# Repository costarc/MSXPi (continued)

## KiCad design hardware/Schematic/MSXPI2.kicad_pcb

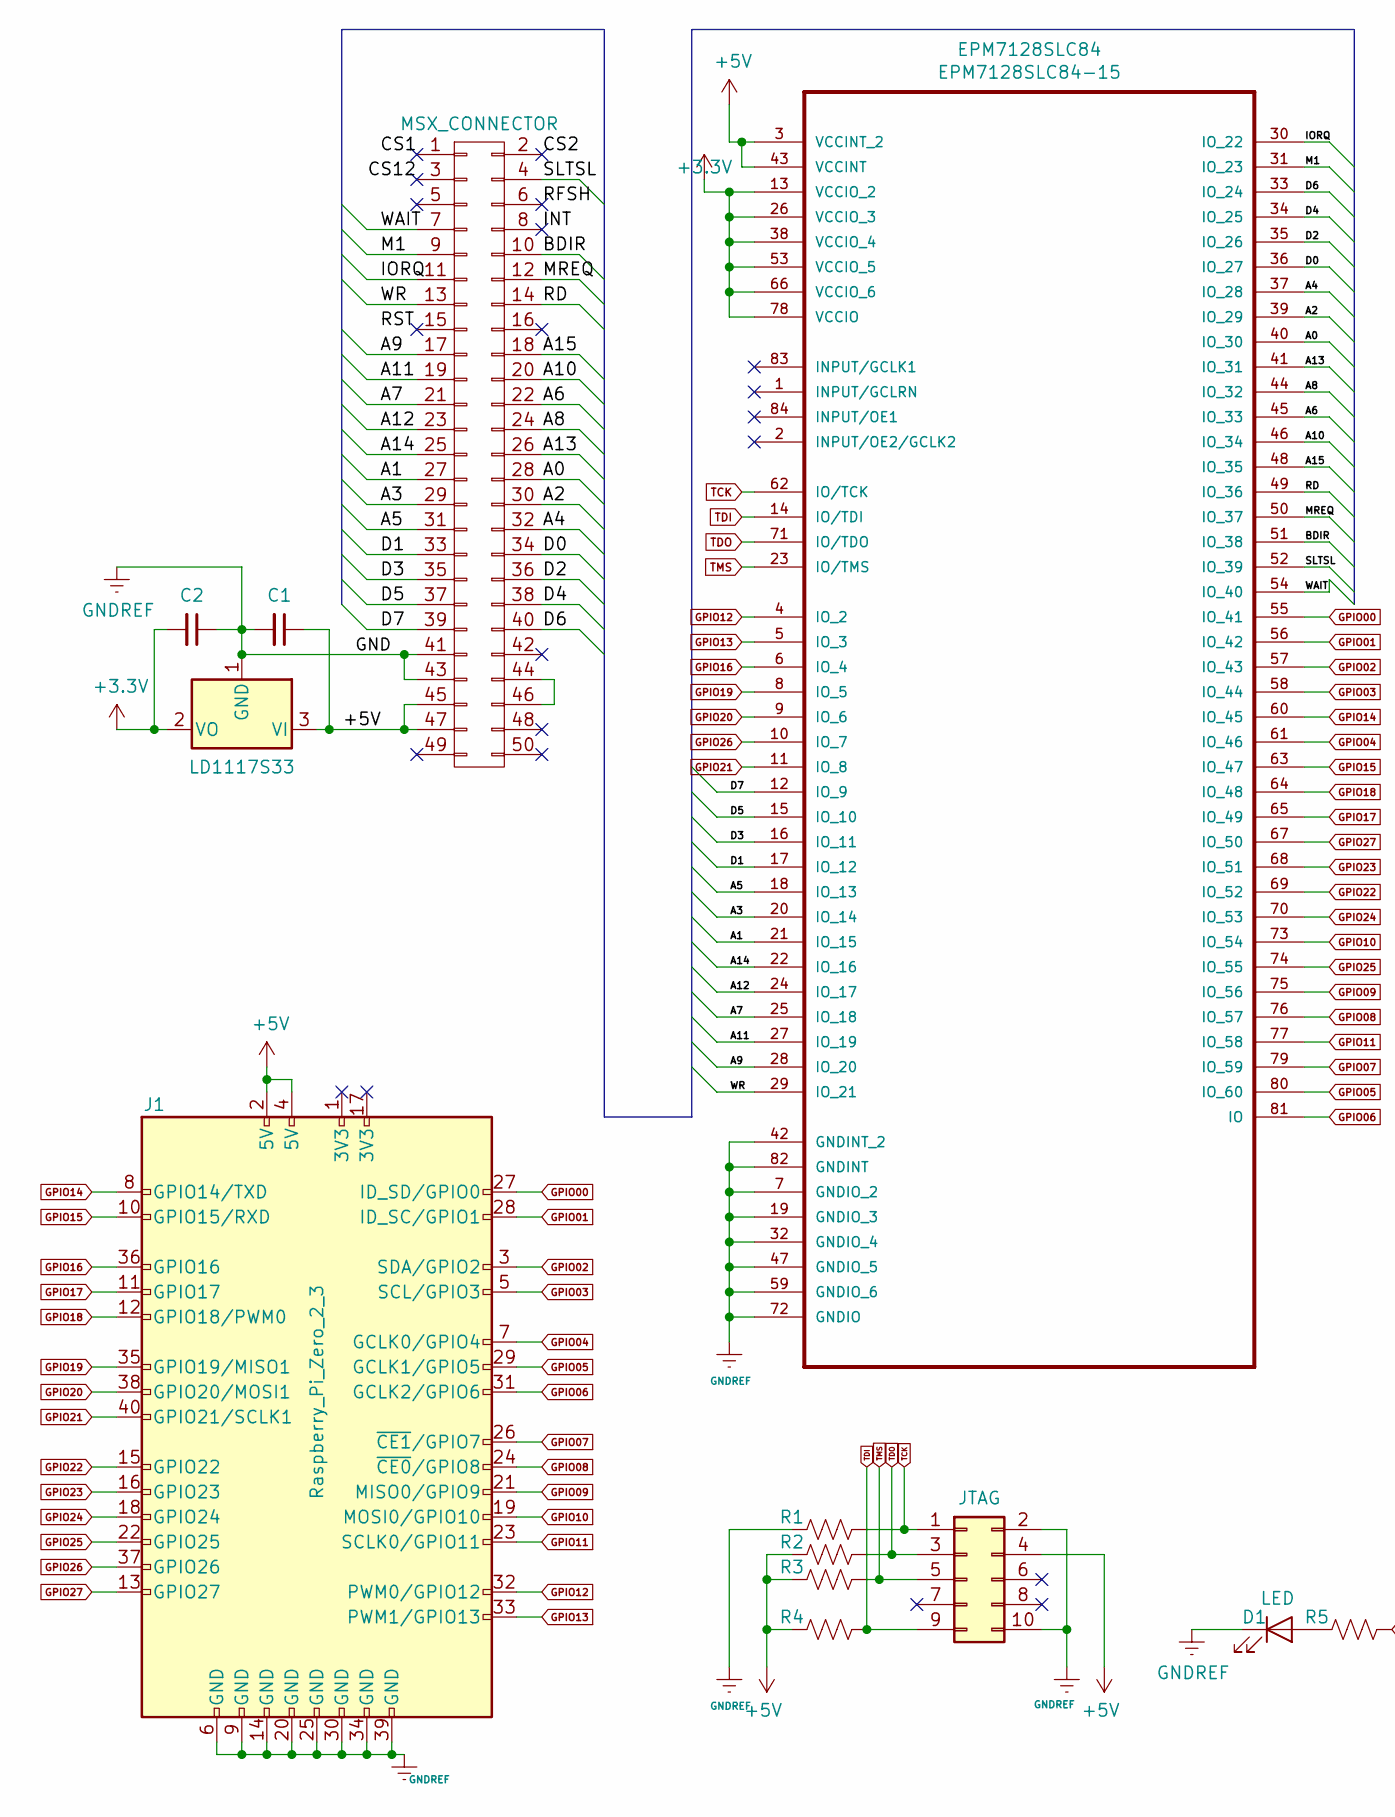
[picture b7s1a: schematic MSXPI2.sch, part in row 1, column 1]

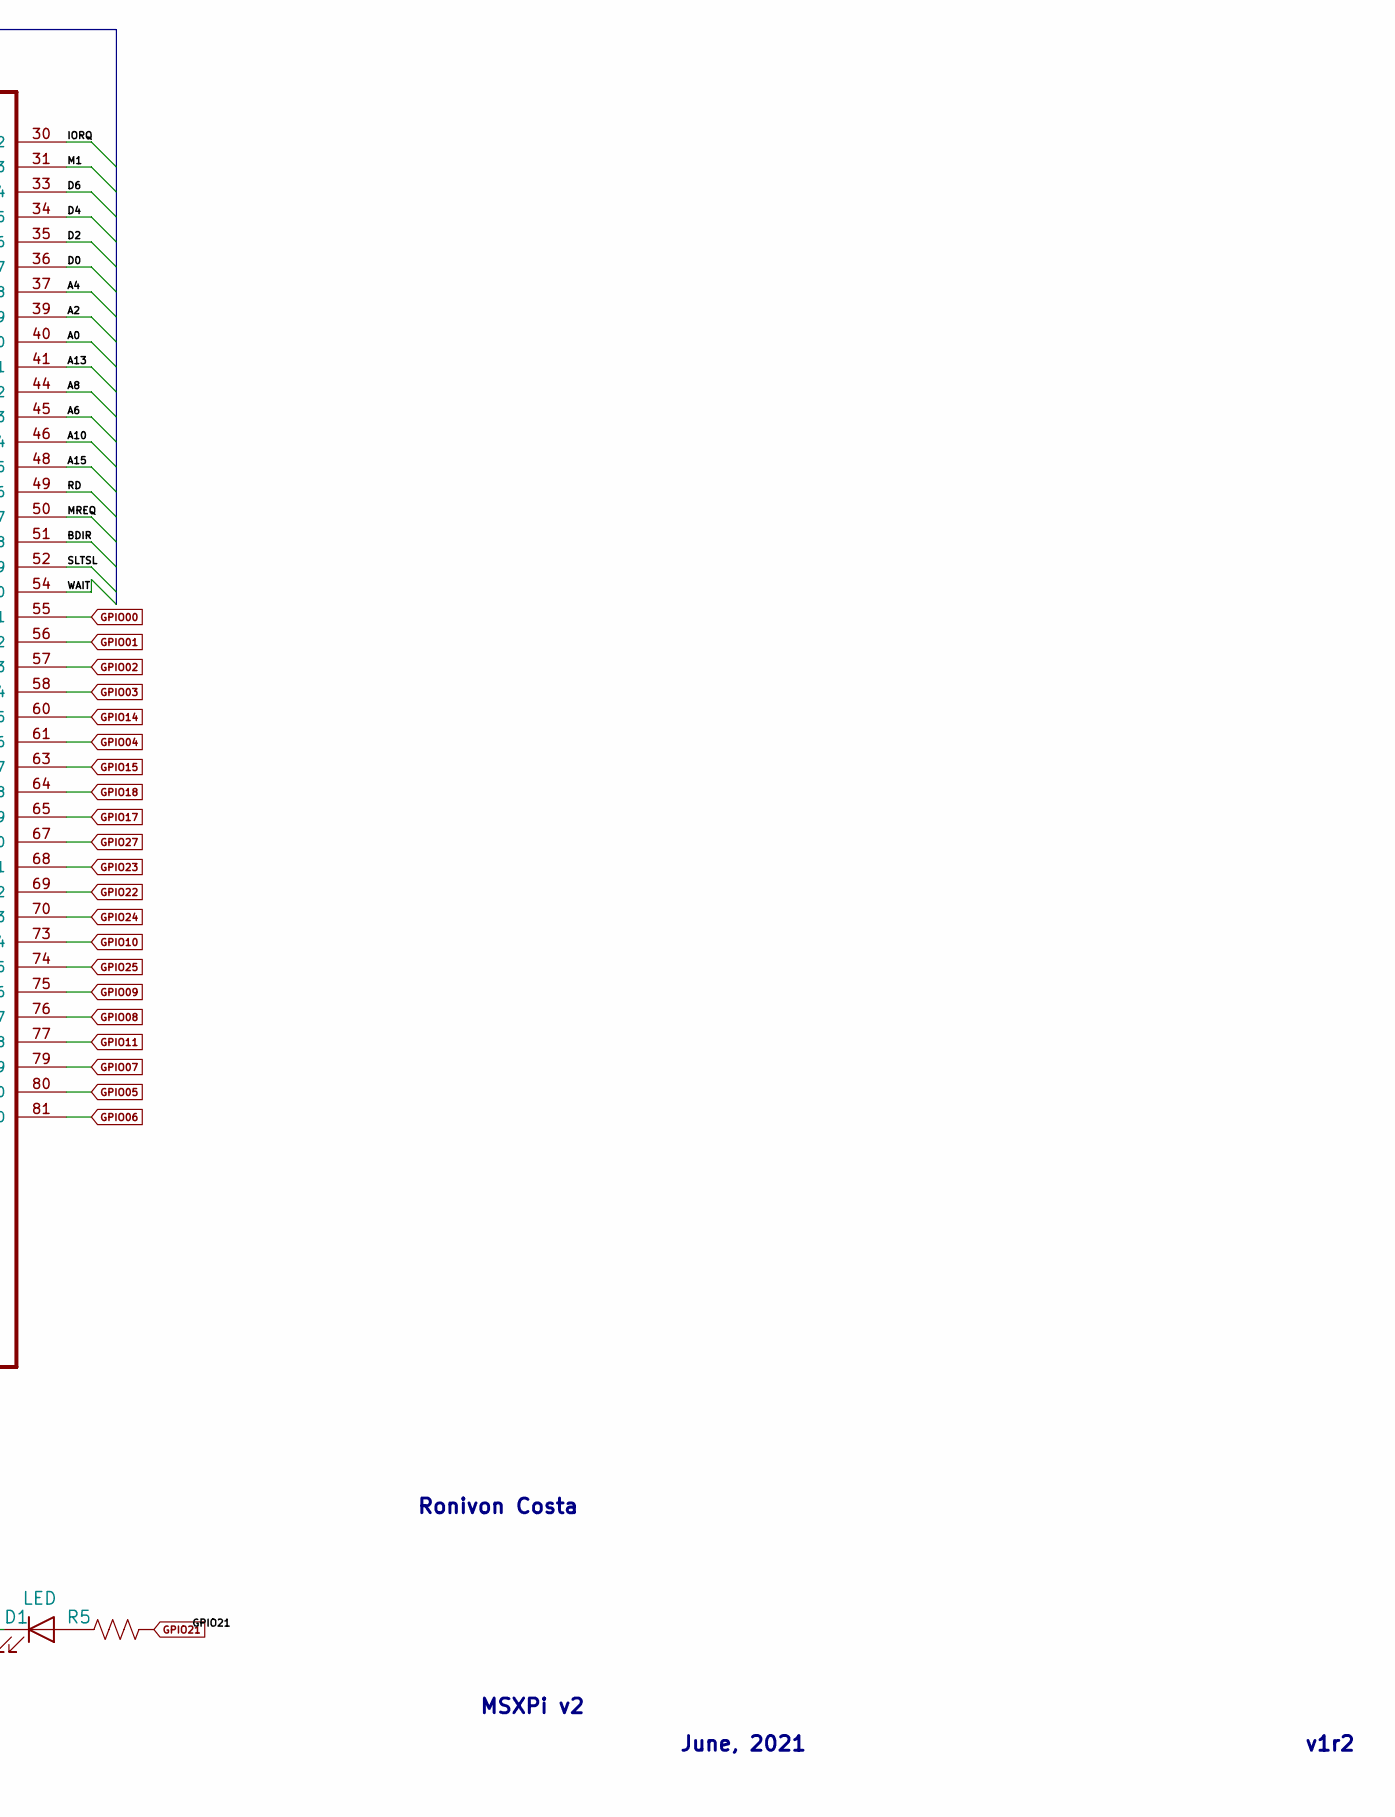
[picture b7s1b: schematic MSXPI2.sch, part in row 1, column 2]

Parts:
C1: C1; C_Disc_D3.0mm_W1.6mm_P2.50mm
C2: C2; C_Disc_D3.0mm_W1.6mm_P2.50mm
D1: LED; LED_D3.0mm
EPM7128SLC84: EPM7128SLC84-15; PLCC-84_THT-Socket
J1: Raspberry_Pi_Zero_2_3; PinHeader_2x20_P2.54mm_Vertical
J2: JTAG; PinHeader_2x05_P2.54mm_Vertical
LD1117S33: LD1117S33TR_SOT223; SOT-223-3_TabPin2
P1: MSX_CONNECTOR; card_edge_connector
R1, R2, R3, R4, R5: R_US; R_Axial_DIN0204_L3.6mm_D1.6mm_P5.08mm_Horizontal

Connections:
+3V3: C2.2, EPM7128SLC84.13 (VCCIO_2), EPM7128SLC84.26 (VCCIO_3), EPM7128SLC84.38 (VCCIO_4), EPM7128SLC84.53 (VCCIO_5), EPM7128SLC84.66 (VCCIO_6), EPM7128SLC84.78 (VCCIO), LD1117S33.2 (VO)
+5V: C1.1, EPM7128SLC84.3 (VCCINT_2), EPM7128SLC84.43 (VCCINT), J1.2 (5V), J1.4 (5V), J2.4, LD1117S33.3 (VI), P1.45, P1.47, R2.2, R3.2, R4.2
/A0: EPM7128SLC84.40 (IO_30), P1.28
/A1: EPM7128SLC84.21 (IO_15), P1.27
/A2: EPM7128SLC84.39 (IO_29), P1.30
/A3: EPM7128SLC84.20 (IO_14), P1.29
/A4: EPM7128SLC84.37 (IO_28), P1.32
/A5: EPM7128SLC84.18 (IO_13), P1.31
/A6: EPM7128SLC84.45 (IO_33), P1.22
/A7: EPM7128SLC84.25 (IO_18), P1.21
/A8: EPM7128SLC84.44 (IO_32), P1.24
/A9: EPM7128SLC84.28 (IO_20), P1.17
/A10: EPM7128SLC84.46 (IO_34), P1.20
/A11: EPM7128SLC84.27 (IO_19), P1.19
/A12: EPM7128SLC84.24 (IO_17), P1.23
/A13: EPM7128SLC84.41 (IO_31), P1.26
/A14: EPM7128SLC84.22 (IO_16), P1.25
/A15: EPM7128SLC84.48 (IO_35), P1.18
/BDIR: EPM7128SLC84.51 (IO_38), P1.10
/D0: EPM7128SLC84.36 (IO_27), P1.34
/D1: EPM7128SLC84.17 (IO_12), P1.33
/D2: EPM7128SLC84.35 (IO_26), P1.36
/D3: EPM7128SLC84.16 (IO_11), P1.35
/D4: EPM7128SLC84.34 (IO_25), P1.38
/D5: EPM7128SLC84.15 (IO_10), P1.37
/D6: EPM7128SLC84.33 (IO_24), P1.40
/D7: EPM7128SLC84.12 (IO_9), P1.39
/IORQ: EPM7128SLC84.30 (IO_22), P1.11
/M1: EPM7128SLC84.31 (IO_23), P1.9
/MREQ: EPM7128SLC84.50 (IO_37), P1.12
/RD: EPM7128SLC84.49 (IO_36), P1.14
/SLTSL: EPM7128SLC84.52 (IO_39), P1.4
/WAIT: EPM7128SLC84.54 (IO_40), P1.7
/WR: EPM7128SLC84.29 (IO_21), P1.13
GNDREF: C1.2, C2.1, D1.1 (K), EPM7128SLC84.7 (GNDIO_2), EPM7128SLC84.19 (GNDIO_3), EPM7128SLC84.32 (GNDIO_4), EPM7128SLC84.42 (GNDINT_2), EPM7128SLC84.47 (GNDIO_5), EPM7128SLC84.59 (GNDIO_6), EPM7128SLC84.72 (GNDIO), EPM7128SLC84.82 (GNDINT), J1.6 (GND), J1.9 (GND), J1.14 (GND), J1.20 (GND), J1.25 (GND), J1.30 (GND), J1.34 (GND), J1.39 (GND), J2.2, J2.10, LD1117S33.1 (GND), P1.41, P1.43, R1.1
GPIO0: EPM7128SLC84.55 (IO_41), J1.27 (ID_SD/GPIO0)
GPIO1: EPM7128SLC84.56 (IO_42), J1.28 (ID_SC/GPIO1)
GPIO02: EPM7128SLC84.57 (IO_43), J1.3 (SDA/GPIO2)
GPIO03: EPM7128SLC84.58 (IO_44), J1.5 (SCL/GPIO3)
GPIO04: EPM7128SLC84.61 (IO_46), J1.7 (GCLK0/GPIO4)
GPIO05: EPM7128SLC84.80 (IO_60), J1.29 (GCLK1/GPIO5)
GPIO06: EPM7128SLC84.81 (IO), J1.31 (GCLK2/GPIO6)
GPIO07: EPM7128SLC84.79 (IO_59), J1.26 (~CE1~/GPIO7)
GPIO08: EPM7128SLC84.76 (IO_57), J1.24 (~CE0~/GPIO8)
GPIO09: EPM7128SLC84.75 (IO_56), J1.21 (MISO0/GPIO9)
GPIO10: EPM7128SLC84.73 (IO_54), J1.19 (MOSI0/GPIO10)
GPIO11: EPM7128SLC84.77 (IO_58), J1.23 (SCLK0/GPIO11)
GPIO12: EPM7128SLC84.4 (IO_2), J1.32 (PWM0/GPIO12)
GPIO13: EPM7128SLC84.5 (IO_3), J1.33 (PWM1/GPIO13)
GPIO14: EPM7128SLC84.60 (IO_45), J1.8 (GPIO14/TXD)
GPIO15: EPM7128SLC84.63 (IO_47), J1.10 (GPIO15/RXD)
GPIO16: EPM7128SLC84.6 (IO_4), J1.36 (GPIO16)
GPIO17: EPM7128SLC84.65 (IO_49), J1.11 (GPIO17)
GPIO18: EPM7128SLC84.64 (IO_48), J1.12 (GPIO18/PWM0)
GPIO19: EPM7128SLC84.8 (IO_5), J1.35 (GPIO19/MISO1)
GPIO20: EPM7128SLC84.9 (IO_6), J1.38 (GPIO20/MOSI1)
GPIO21: EPM7128SLC84.11 (IO_8), J1.40 (GPIO21/SCLK1), R5.2
GPIO22: EPM7128SLC84.69 (IO_52), J1.15 (GPIO22)
GPIO23: EPM7128SLC84.68 (IO_51), J1.16 (GPIO23)
GPIO24: EPM7128SLC84.70 (IO_53), J1.18 (GPIO24)
GPIO25: EPM7128SLC84.74 (IO_55), J1.22 (GPIO25)
GPIO26: EPM7128SLC84.10 (IO_7), J1.37 (GPIO26)
GPIO27: EPM7128SLC84.67 (IO_50), J1.13 (GPIO27)
unnamed: D1.2 (A), R5.1
unnamed: P1.44, P1.46
TCK: EPM7128SLC84.62 (IO/TCK), J2.1, R1.2
TDI: EPM7128SLC84.14 (IO/TDI), J2.9, R4.1
TDO: EPM7128SLC84.71 (IO/TDO), J2.3, R2.1
TMS: EPM7128SLC84.23 (IO/TMS), J2.5, R3.1

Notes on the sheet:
MSXPi v2
June, 2021
v1r2
Ronivon Costa

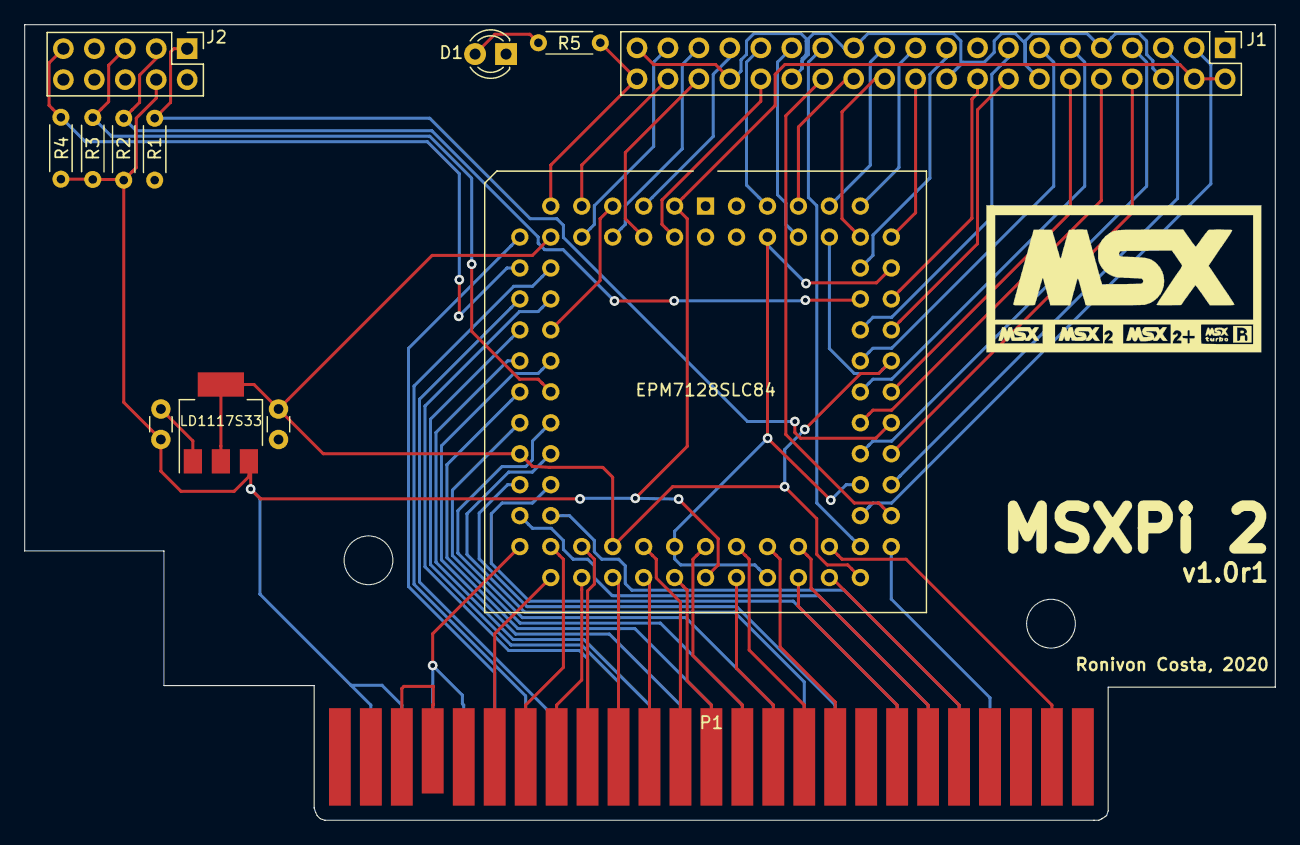
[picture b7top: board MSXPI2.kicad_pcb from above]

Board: 2 copper layers, 102.6 x 65.3 mm, 13 parts (0 on the bottom side), 69 nets.

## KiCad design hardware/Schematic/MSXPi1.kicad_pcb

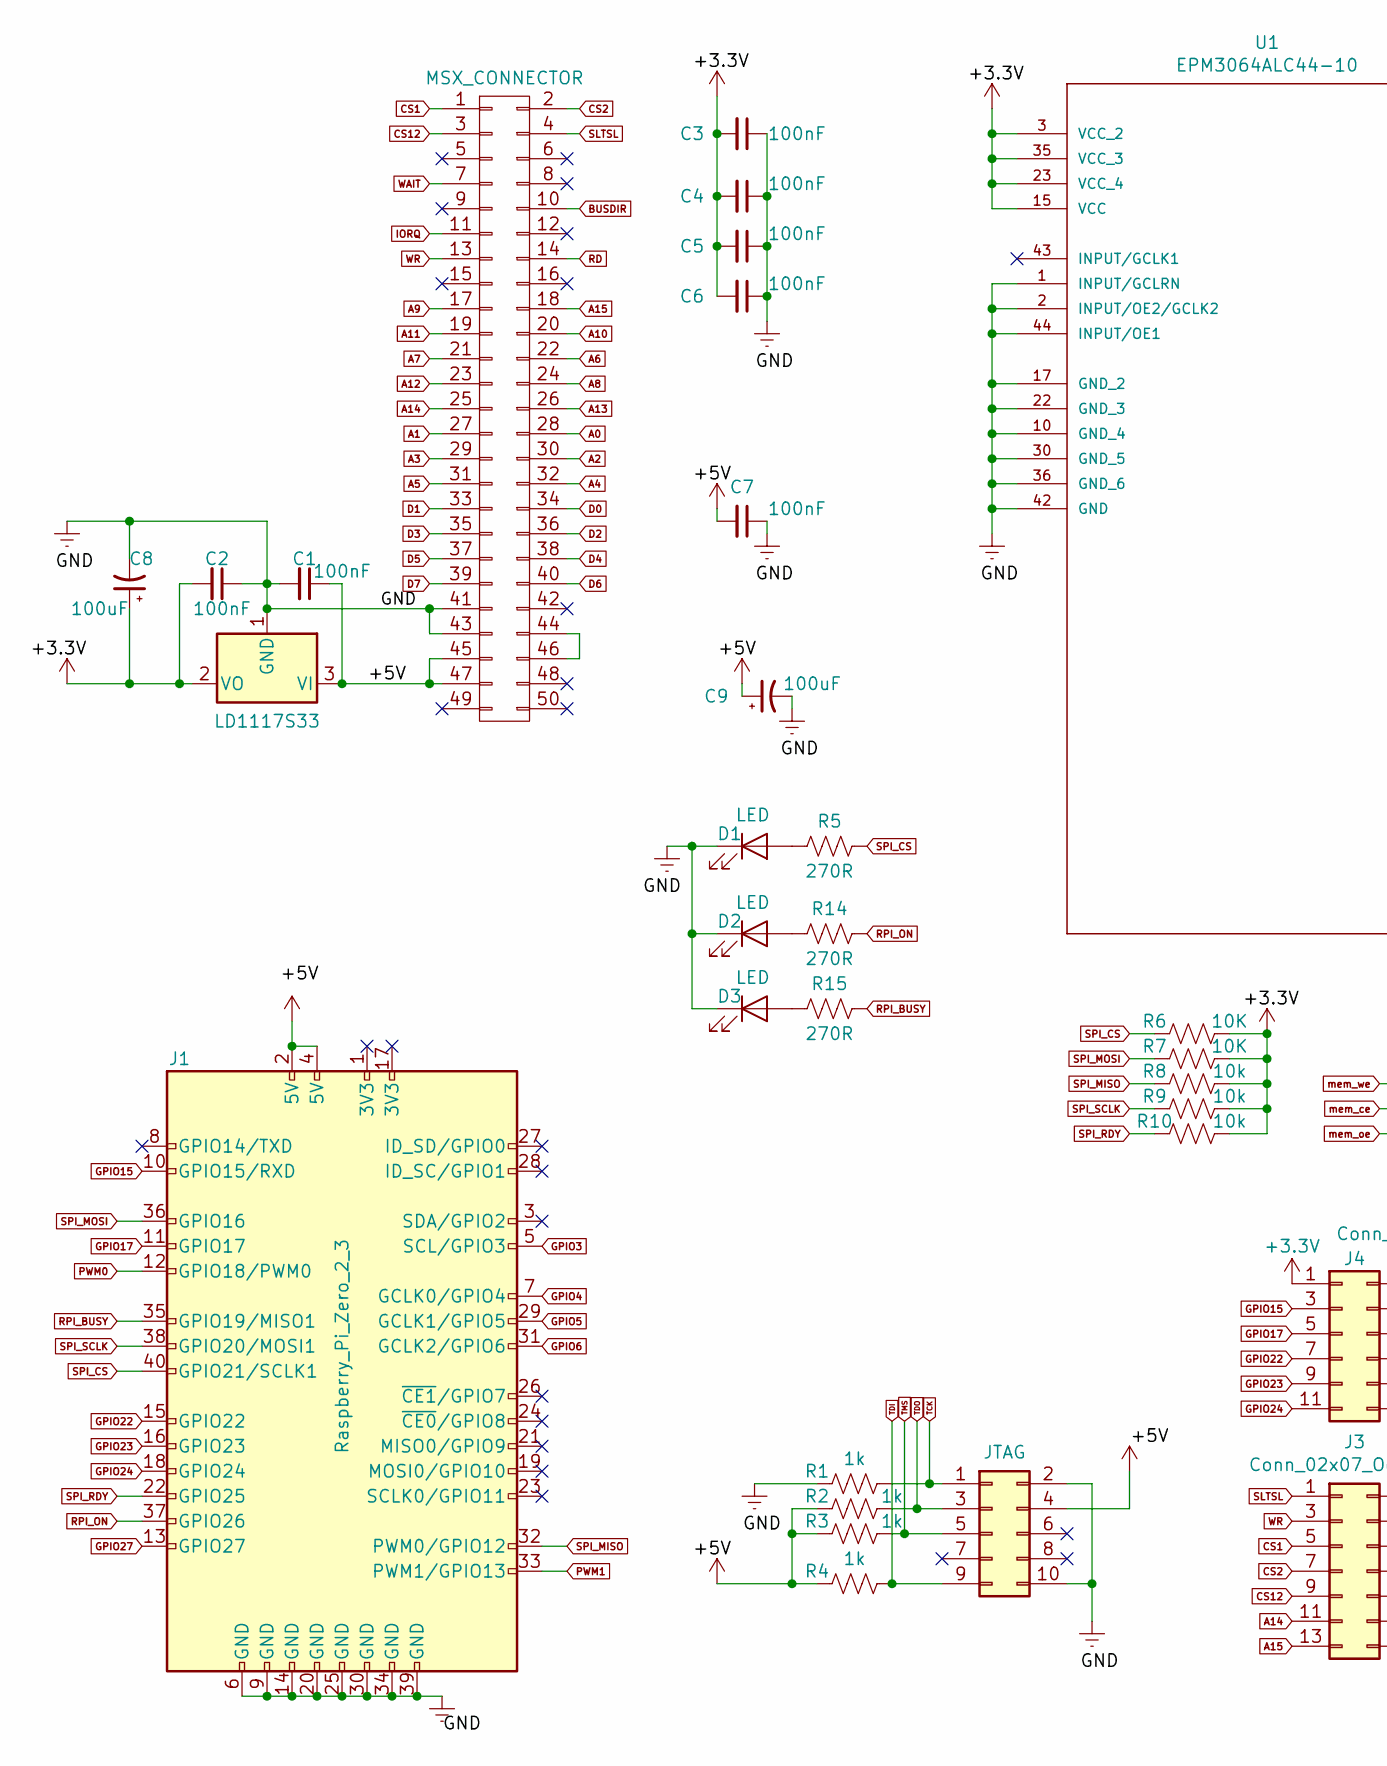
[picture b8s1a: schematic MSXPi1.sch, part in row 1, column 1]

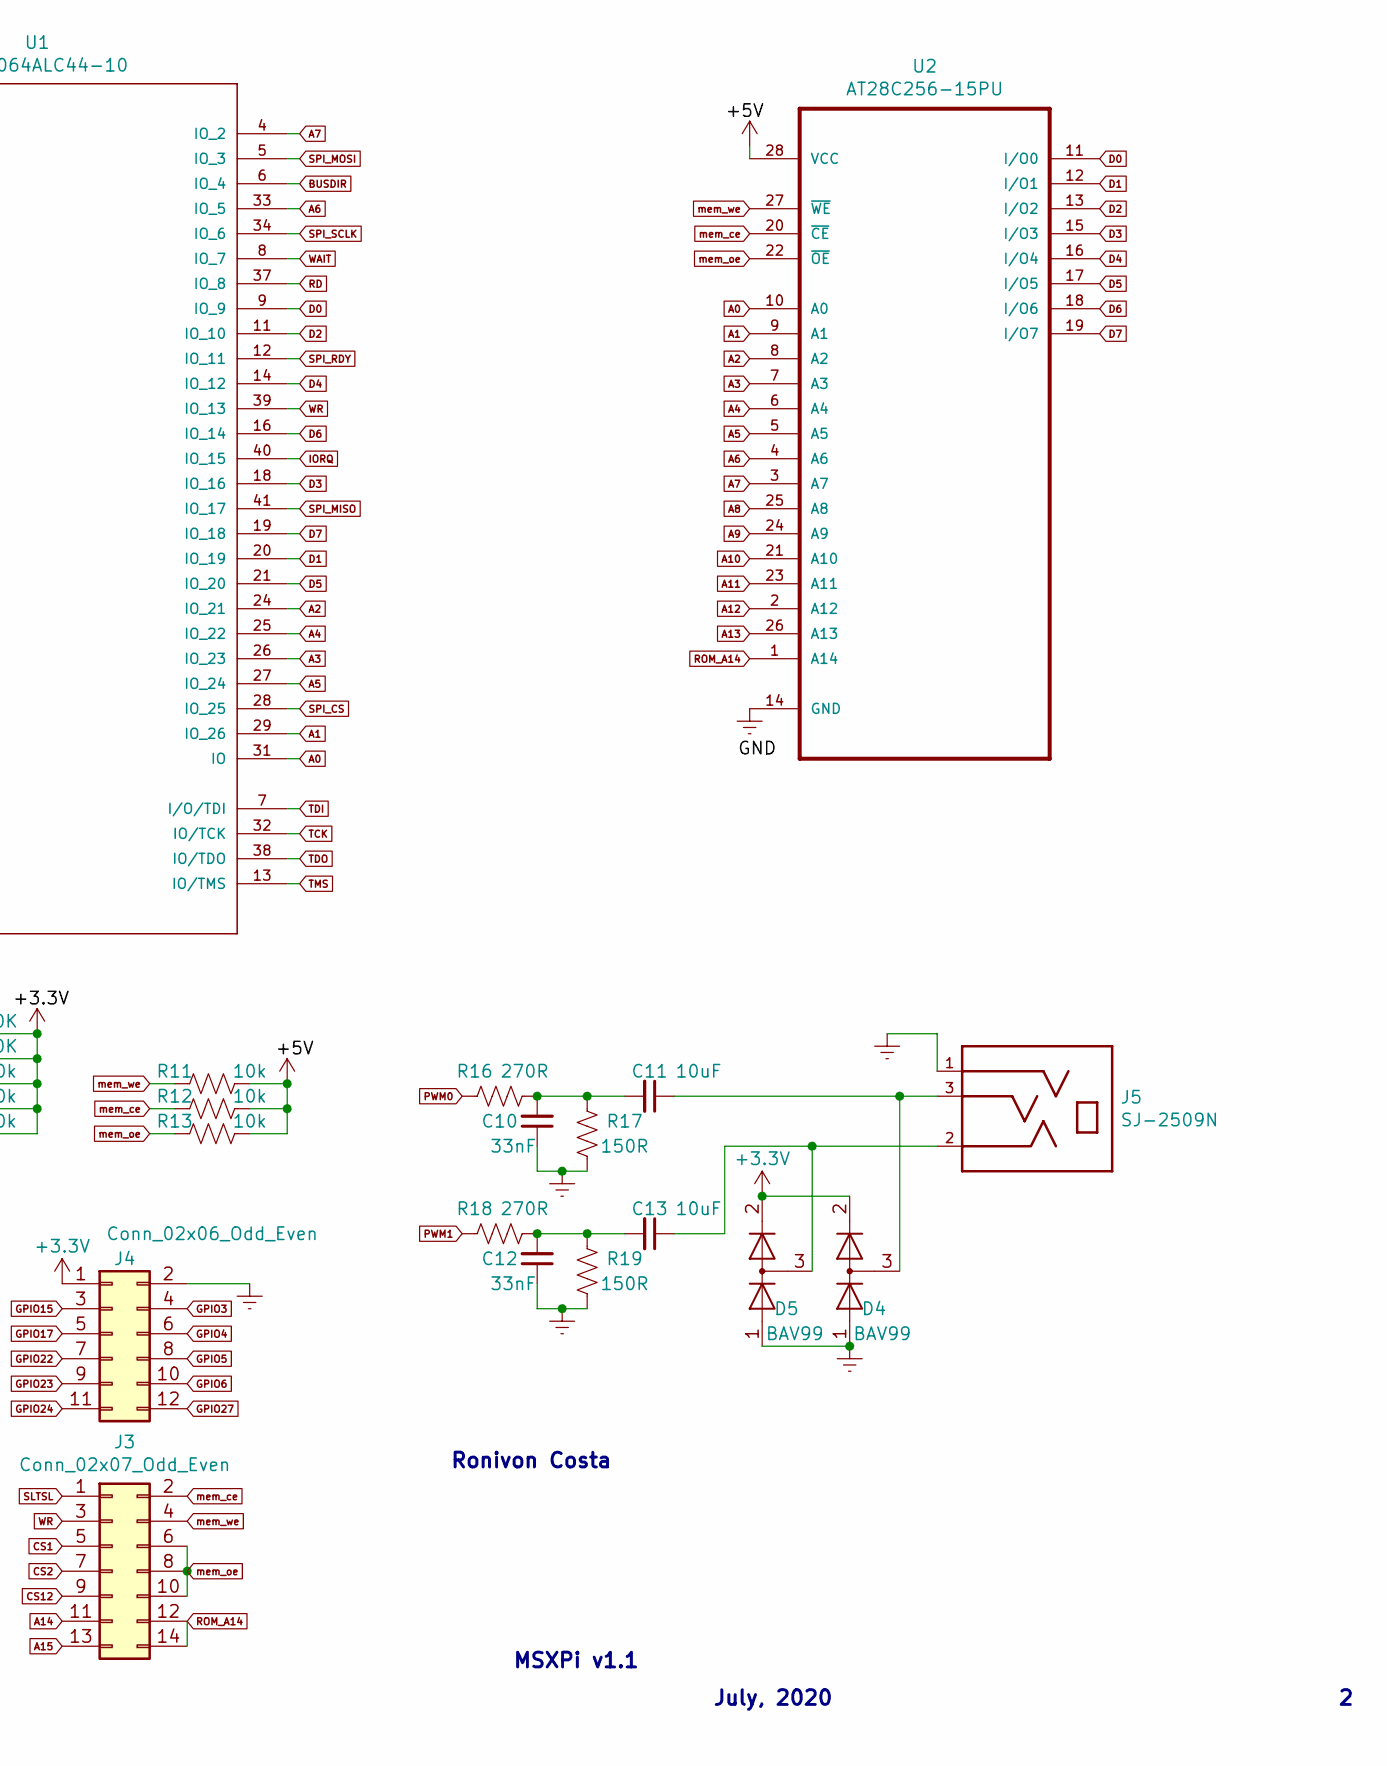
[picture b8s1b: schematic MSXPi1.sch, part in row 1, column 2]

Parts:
C1, C2, C3, C4, C5, C6, C7: 100nF; C_Disc_D3.0mm_W1.6mm_P2.50mm
C8, C9: 100uF; CP_Radial_D5.0mm_P2.50mm
C10, C12: 33nF; C_Disc_D3.0mm_W1.6mm_P2.50mm
C11, C13: 10uF; C_Disc_D3.0mm_W1.6mm_P2.50mm
D1, D2, D3: LED; LED_D3.0mm
D4, D5: BAV99; SOT-23
J1: Raspberry_Pi_Zero_2_3; PinHeader_2x20_P2.54mm_Vertical
J2: JTAG; IDC-Header_2x05_P2.54mm_Horizontal
J3: Conn_02x07_Odd_Even; PinHeader_2x07_P2.54mm_Horizontal
J4: Conn_02x06_Odd_Even; PinHeader_2x06_P2.54mm_Horizontal
J5: SJ-2509N; CUI_SJ-2509N
LD1117S33: LD1117S33TR_SOT223; SOT-223-3_TabPin2
P1: MSX_CONNECTOR; card_edge_connector
R1, R2, R3, R4: 1k; R_Axial_DIN0204_L3.6mm_D1.6mm_P5.08mm_Horizontal
R5, R14, R15, R16, R18: 270R; R_Axial_DIN0204_L3.6mm_D1.6mm_P5.08mm_Horizontal
R6, R7: 10K; R_Axial_DIN0204_L3.6mm_D1.6mm_P5.08mm_Horizontal
R8, R9, R10, R11, R12, R13: 10k; R_Axial_DIN0204_L3.6mm_D1.6mm_P5.08mm_Horizontal
R17, R19: 150R; R_Axial_DIN0204_L3.6mm_D1.6mm_P5.08mm_Horizontal
U1: EPM3064ALC44-10; PLCC127P1765X1765X457-44N
U2: AT28C256-15PU; DIP254P1524X482-28

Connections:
+3V3: C2.2, C3.2, C4.2, C5.2, C6.2, C8.1, D4.2 (A), D5.2 (A), J4.1, LD1117S33.2 (VO), R6.2, R7.2, R8.2, R9.2, R10.2, U1.3 (VCC_2), U1.15 (VCC), U1.23 (VCC_4), U1.35 (VCC_3)
+5V: C1.1, C7.2, C9.1, J1.2 (5V), J1.4 (5V), J2.4, LD1117S33.3 (VI), P1.45, P1.47, R2.2, R3.2, R4.2, R11.2, R12.2, R13.2, U2.28 (VCC); also elsewhere on the board
A0: P1.28, U1.31 (IO), U2.10 (A0); also elsewhere on the board
A1: P1.27, U1.29 (IO_26), U2.9 (A1); also elsewhere on the board
A2: P1.30, U1.24 (IO_21), U2.8 (A2); also elsewhere on the board
A3: P1.29, U1.26 (IO_23), U2.7 (A3); also elsewhere on the board
A4: P1.32, U1.25 (IO_22), U2.6 (A4); also elsewhere on the board
A5: P1.31, U1.27 (IO_24), U2.5 (A5); also elsewhere on the board
A6: P1.22, U1.33 (IO_5), U2.4 (A6); also elsewhere on the board
A7: P1.21, U1.4 (IO_2), U2.3 (A7); also elsewhere on the board
A8: P1.24, U2.25 (A8); also elsewhere on the board
A9: P1.17, U2.24 (A9); also elsewhere on the board
A10: P1.20, U2.21 (A10); also elsewhere on the board
A11: P1.19, U2.23 (A11); also elsewhere on the board
A12: P1.23, U2.2 (A12); also elsewhere on the board
A13: P1.26, U2.26 (A13); also elsewhere on the board
A14: J3.11, P1.25
A15: J3.13, P1.18
BUSDIR: P1.10, U1.6 (IO_4)
CS1: J3.5, P1.1
CS2: J3.7, P1.2
CS12: J3.9, P1.3
D0: P1.34, U1.9 (IO_9), U2.11 (I/O0); also elsewhere on the board
D1: P1.33, U1.20 (IO_19), U2.12 (I/O1); also elsewhere on the board
D2: P1.36, U1.11 (IO_10), U2.13 (I/O2); also elsewhere on the board
D3: P1.35, U1.18 (IO_16), U2.15 (I/O3); also elsewhere on the board
D4: P1.38, U1.14 (IO_12), U2.16 (I/O4); also elsewhere on the board
D5: P1.37, U1.21 (IO_20), U2.17 (I/O5); also elsewhere on the board
D6: P1.40, U1.16 (IO_14), U2.18 (I/O6); also elsewhere on the board
D7: P1.39, U1.19 (IO_18), U2.19 (I/O7); also elsewhere on the board
GNDREF: C1.2, C2.1, C3.1, C4.1, C5.1, C6.1, C7.1, C8.2, C9.2, C10.1, C12.1, D1.1 (K), D2.1 (K), D3.1 (K), D4.1 (K), D5.1 (K), J1.6 (GND), J1.9 (GND), J1.14 (GND), J1.20 (GND), J1.25 (GND), J1.30 (GND), J1.34 (GND), J1.39 (GND), J2.2, J2.10, J4.2, J5.1, LD1117S33.1 (GND), P1.41, P1.43, R1.1, R17.2, R19.2, U1.1 (INPUT/GCLRN), U1.2 (INPUT/OE2/GCLK2), U1.10 (GND_4), U1.17 (GND_2), U1.22 (GND_3), U1.30 (GND_5), U1.36 (GND_6), U1.42 (GND), U1.44 (INPUT/OE1), U2.14 (GND); also elsewhere on the board
GPIO3: J1.5 (SCL/GPIO3), J4.4
GPIO4: J1.7 (GCLK0/GPIO4), J4.6
GPIO5: J1.29 (GCLK1/GPIO5), J4.8
GPIO6: J1.31 (GCLK2/GPIO6), J4.10
GPIO15: J1.10 (GPIO15/RXD), J4.3
GPIO17: J1.11 (GPIO17), J4.5
GPIO22: J1.15 (GPIO22), J4.7
GPIO23: J1.16 (GPIO23), J4.9
GPIO24: J1.18 (GPIO24), J4.11
GPIO27: J1.13 (GPIO27), J4.12
IORQ: P1.11, U1.40 (IO_15)
unnamed: C10.2, C11.2, R16.2, R17.1
unnamed: C11.1, D4.3 (K), J5.3
unnamed: C12.2, C13.2, R18.2, R19.1
unnamed: C13.1, D5.3 (K), J5.2
unnamed: D1.2 (A), R5.1
unnamed: D2.2 (A), R14.1
unnamed: D3.2 (A), R15.1
unnamed: P1.44, P1.46
PWM0: J1.12 (GPIO18/PWM0), R16.1
PWM1: J1.33 (PWM1/GPIO13), R18.1
RD: P1.14, U1.37 (IO_8)
ROM_A14: J3.12, J3.14, U2.1 (A14); also elsewhere on the board
RPI_BUSY: J1.35 (GPIO19/MISO1), R15.2
RPI_ON: J1.37 (GPIO26), R14.2
SLTSL: J3.1, P1.4
SPI_CS: J1.40 (GPIO21/SCLK1), R5.2, R6.1, U1.28 (IO_25)
SPI_MISO: J1.32 (PWM0/GPIO12), R8.1, U1.41 (IO_17)
SPI_MOSI: J1.36 (GPIO16), R7.1, U1.5 (IO_3)
SPI_RDY: J1.22 (GPIO25), R10.1, U1.12 (IO_11)
SPI_SCLK: J1.38 (GPIO20/MOSI1), R9.1, U1.34 (IO_6)
TCK: J2.1, R1.2, U1.32 (IO/TCK)
TDI: J2.9, R4.1, U1.7 (I/O/TDI)
TDO: J2.3, R2.1, U1.38 (IO/TDO)
TMS: J2.5, R3.1, U1.13 (IO/TMS)
WAIT: P1.7, U1.8 (IO_7)
WR: J3.3, P1.13, U1.39 (IO_13)
mem_ce: J3.2, R12.1, U2.20 (~CE); also elsewhere on the board
mem_oe: J3.6, J3.8, J3.10, R13.1, U2.22 (~OE); also elsewhere on the board
mem_we: J3.4, R11.1, U2.27 (~WE); also elsewhere on the board

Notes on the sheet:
MSXPi v1.1
July, 2020
Ronivon Costa

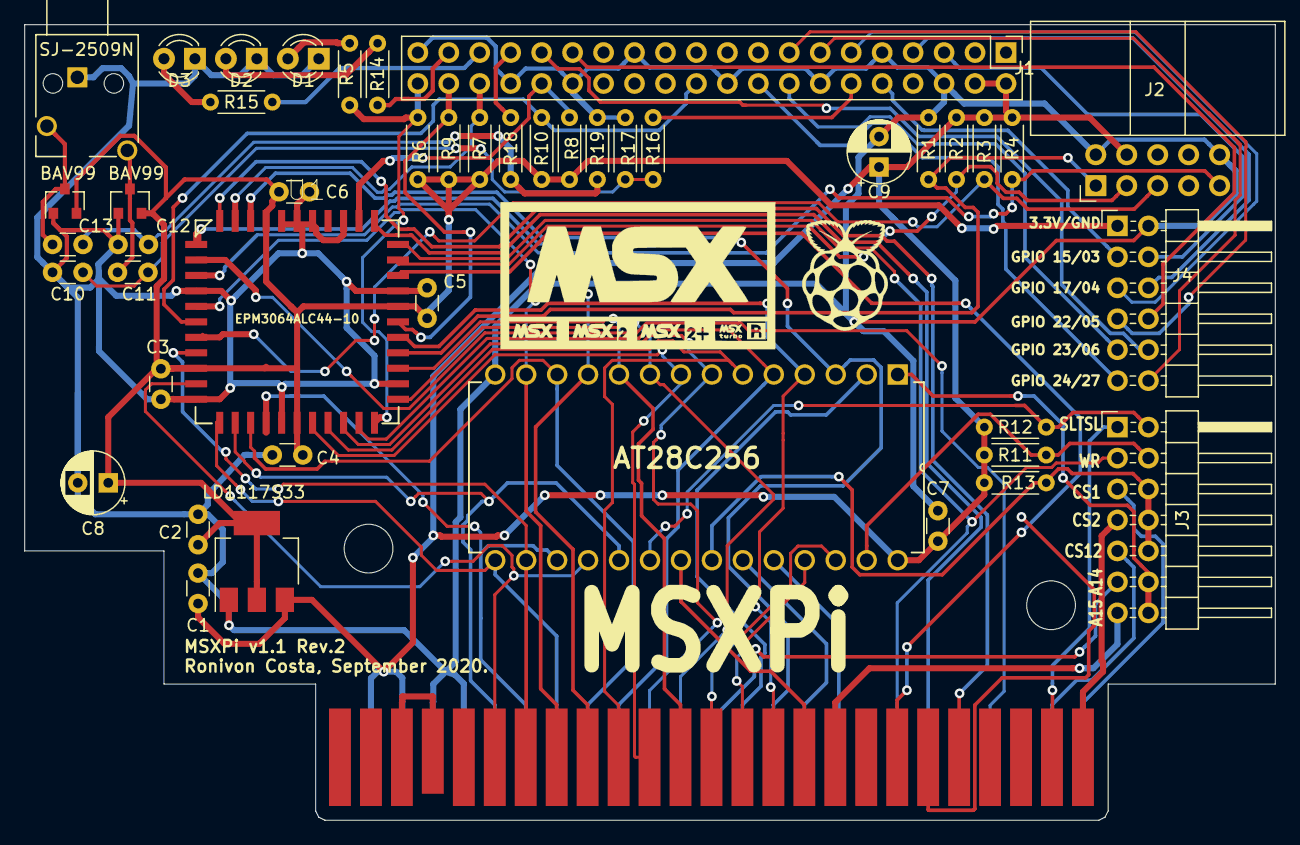
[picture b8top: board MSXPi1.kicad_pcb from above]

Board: 2 copper layers, 102.6 x 65.3 mm, 46 parts (0 on the bottom side), 71 nets.

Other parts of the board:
AT28C256: AT28C256-15PU; DIP254P1524X482-28

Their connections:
+5V: AT28C256.28; also elsewhere on the board
A0: AT28C256.10; also elsewhere on the board
A1: AT28C256.9; also elsewhere on the board
A2: AT28C256.8; also elsewhere on the board
A3: AT28C256.7; also elsewhere on the board
A4: AT28C256.6; also elsewhere on the board
A5: AT28C256.5; also elsewhere on the board
A6: AT28C256.4; also elsewhere on the board
A7: AT28C256.3; also elsewhere on the board
A8: AT28C256.25; also elsewhere on the board
A9: AT28C256.24; also elsewhere on the board
A10: AT28C256.21; also elsewhere on the board
A11: AT28C256.23; also elsewhere on the board
A12: AT28C256.2; also elsewhere on the board
A13: AT28C256.26; also elsewhere on the board
D0: AT28C256.11; also elsewhere on the board
D1: AT28C256.12; also elsewhere on the board
D2: AT28C256.13; also elsewhere on the board
D3: AT28C256.15; also elsewhere on the board
D4: AT28C256.16; also elsewhere on the board
D5: AT28C256.17; also elsewhere on the board
D6: AT28C256.18; also elsewhere on the board
D7: AT28C256.19; also elsewhere on the board
GNDREF: AT28C256.14; also elsewhere on the board
ROM_A14: AT28C256.1; also elsewhere on the board
mem_ce: AT28C256.20; also elsewhere on the board
mem_oe: AT28C256.22; also elsewhere on the board
mem_we: AT28C256.27; also elsewhere on the board

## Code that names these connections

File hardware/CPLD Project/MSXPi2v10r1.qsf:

# -------------------------------------------------------------------------- #
#
# Copyright (C) 1991-2013 Altera Corporation
# Your use of Altera Corporation's design tools, logic functions 
# and other software and tools, and its AMPP partner logic 
# functions, and any output files from any of the foregoing 
# (including device programming or simulation files), and any 
# associated documentation or information are expressly subject 
# to the terms and conditions of the Altera Program License 
# Subscription Agreement, Altera MegaCore Function License 
# Agreement, or other applicable license agreement, including, 
# without limitation, that your use is for the sole purpose of 
# programming logic devices manufactured by Altera and sold by 
# Altera or its authorized distributors.  Please refer to the 
# applicable agreement for further details.
#
# -------------------------------------------------------------------------- #
#
# Quartus II 64-Bit
# Version 13.0.1 Build 232 06/12/2013 Service Pack 1 SJ Web Edition
# Date created = 17:53:13  June 01, 2021
#
# -------------------------------------------------------------------------- #
#
# Notes:
#
# 1) The default values for assignments are stored in the file:
#		MSXPi2v10r1_assignment_defaults.qdf
#    If this file doesn't exist, see file:
#		assignment_defaults.qdf
#
# 2) Altera recommends that you do not modify this file. This
#    file is updated automatically by the Quartus II software
#    and any changes you make may be lost or overwritten.
#
# -------------------------------------------------------------------------- #


set_global_assignment -name FAMILY MAX7000S
set_global_assignment -name DEVICE "EPM7128SLC84-15"
set_global_assignment -name TOP_LEVEL_ENTITY MSXPi2v10r1
set_global_assignment -name ORIGINAL_QUARTUS_VERSION "13.0 SP1"
set_global_assignment -name PROJECT_CREATION_TIME_DATE "17:53:13  JUNE 01, 2021"
set_global_assignment -name LAST_QUARTUS_VERSION "13.0 SP1"
set_global_assignment -name PROJECT_OUTPUT_DIRECTORY output_files
set_global_assignment -name DEVICE_FILTER_PIN_COUNT 84
set_global_assignment -name ERROR_CHECK_FREQUENCY_DIVISOR "-1"
set_global_assignment -name MIN_CORE_JUNCTION_TEMP 0
set_global_assignment -name MAX_CORE_JUNCTION_TEMP 85
set_global_assignment -name MAX7000_DEVICE_IO_STANDARD TTL
set_location_assignment PIN_1 -to NC_01
set_location_assignment PIN_4 -to GPIO12
set_location_assignment PIN_5 -to GPIO13
set_location_assignment PIN_6 -to GPIO16
set_location_assignment PIN_8 -to GPIO19
set_location_assignment PIN_9 -to GPIO20
set_location_assignment PIN_10 -to GPIO26
set_location_assignment PIN_11 -to GPIO21
set_location_assignment PIN_12 -to D7
set_location_assignment PIN_15 -to D5
set_location_assignment PIN_16 -to D3
set_location_assignment PIN_17 -to D1
set_location_assignment PIN_18 -to A5
set_location_assignment PIN_20 -to A3
set_location_assignment PIN_22 -to A14
set_location_assignment PIN_24 -to A12
set_location_assignment PIN_25 -to A7
set_location_assignment PIN_27 -to A11
set_location_assignment PIN_28 -to A9
set_location_assignment PIN_29 -to WR_N
set_location_assignment PIN_30 -to IORQ_N
set_location_assignment PIN_33 -to D6
set_location_assignment PIN_34 -to D4
set_location_assignment PIN_35 -to D2
set_location_assignment PIN_36 -to D0
set_location_assignment PIN_37 -to A4
set_location_assignment PIN_39 -to A2
set_location_assignment PIN_40 -to A0
set_location_assignment PIN_41 -to A13
set_location_assignment PIN_44 -to A8
set_location_assignment PIN_45 -to A6
set_location_assignment PIN_46 -to A10
set_location_assignment PIN_48 -to A15
set_location_assignment PIN_49 -to RD_N
set_location_assignment PIN_50 -to MREQ_N
set_location_assignment PIN_51 -to BDIR_N
set_location_assignment PIN_52 -to SLTSL_N
set_location_assignment PIN_54 -to WAIT_N
set_location_assignment PIN_55 -to GPIO0
set_location_assignment PIN_56 -to GPIO1
set_location_assignment PIN_57 -to GPIO2
set_location_assignment PIN_58 -to GPIO3
set_location_assignment PIN_60 -to GPIO14
set_location_assignment PIN_63 -to GPIO15
set_location_assignment PIN_64 -to GPIO18
set_location_assignment PIN_65 -to GPIO17
set_location_assignment PIN_67 -to GPIO27
set_location_assignment PIN_68 -to GPIO23
set_location_assignment PIN_69 -to GPIO22
set_location_assignment PIN_70 -to GPIO24
set_location_assignment PIN_73 -to GPIO10
set_location_assignment PIN_74 -to GPIO25
set_location_assignment PIN_75 -to GPIO9
set_location_assignment PIN_76 -to GPIO8
set_location_assignment PIN_77 -to GPIO11
set_location_assignment PIN_79 -to GPIO7
set_location_assignment PIN_80 -to GPIO5
set_location_assignment PIN_81 -to GPIO6
set_location_assignment PIN_84 -to NC_84
set_global_assignment -name VHDL_FILE MSXPi2v10r1.vhd
set_location_assignment PIN_31 -to M1_N

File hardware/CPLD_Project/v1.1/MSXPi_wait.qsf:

# MSXPi v1.6 CPLD firmware - v1.1 and v1.2.1b boards (PCB V1.1 Rev.1 and V1.2.1b, AT28C256 EEPROM, pin map B)
# Build: /WAIT, build ID $14.  pin 28 = WAIT_n, must reach slot pin 7 (/WAIT).
# Pin map taken from the fitted pin report of the original release for this board,
# BUSDIR_n is pinned explicitly (the v1.1 original left it to the fitter).

set_global_assignment -name FAMILY MAX3000A
set_global_assignment -name DEVICE "EPM3064ALC44-10"
set_global_assignment -name TOP_LEVEL_ENTITY MSXPi
set_global_assignment -name ORIGINAL_QUARTUS_VERSION "13.0 SP1"
set_global_assignment -name PROJECT_CREATION_TIME_DATE "02:06:52  OCTOBER 15, 2020"
set_global_assignment -name LAST_QUARTUS_VERSION "13.0 SP1"
set_global_assignment -name USE_GENERATED_PHYSICAL_CONSTRAINTS OFF -section_id eda_palace
set_global_assignment -name MAX7000_OPTIMIZATION_TECHNIQUE AREA
set_global_assignment -name OPTIMIZE_HOLD_TIMING OFF
set_global_assignment -name FITTER_EFFORT "STANDARD FIT"
set_global_assignment -name AUTO_PARALLEL_EXPANDERS OFF
set_global_assignment -name SYNTH_TIMING_DRIVEN_SYNTHESIS OFF
set_global_assignment -name OPTIMIZE_MULTI_CORNER_TIMING OFF
set_global_assignment -name STATE_MACHINE_PROCESSING "MINIMAL BITS"
set_global_assignment -name SAFE_STATE_MACHINE ON
set_global_assignment -name LIMIT_AHDL_INTEGERS_TO_32_BITS ON
set_global_assignment -name ALM_REGISTER_PACKING_EFFORT HIGH
set_global_assignment -name MAX_LABS 20
set_global_assignment -name DEVICE_FILTER_PACKAGE PLCC
set_global_assignment -name MAX7000_DEVICE_IO_STANDARD "3.3-V LVTTL"
set_global_assignment -name FORCE_FITTER_TO_AVOID_PERIPHERY_PLACEMENT_WARNINGS OFF
set_global_assignment -name OPTIMIZE_IOC_REGISTER_PLACEMENT_FOR_TIMING NORMAL
set_global_assignment -name ECO_REGENERATE_REPORT ON
set_global_assignment -name EDA_SIMULATION_TOOL "ModelSim-Altera (VHDL)"
set_global_assignment -name EDA_TIME_SCALE "1 ps" -section_id eda_simulation
set_global_assignment -name EDA_OUTPUT_DATA_FORMAT VHDL -section_id eda_simulation
set_global_assignment -name TIMEQUEST_MULTICORNER_ANALYSIS OFF
set_global_assignment -name FLOW_ENABLE_IO_ASSIGNMENT_ANALYSIS OFF
set_global_assignment -name SMART_RECOMPILE ON
set_global_assignment -name VHDL_FILE ../MSXPi.vhd
set_global_assignment -name VHDL_FILE MSXPi_package_wait.vhd

set_location_assignment PIN_20 -to D[0]
set_location_assignment PIN_37 -to D[1]
set_location_assignment PIN_19 -to D[2]
set_location_assignment PIN_39 -to D[3]
set_location_assignment PIN_18 -to D[4]
set_location_assignment PIN_41 -to D[5]
set_location_assignment PIN_11 -to D[6]
set_location_assignment PIN_29 -to D[7]
set_location_assignment PIN_14 -to A[0]
set_location_assignment PIN_34 -to A[1]
set_location_assignment PIN_21 -to A[2]
set_location_assignment PIN_25 -to A[3]
set_location_assignment PIN_16 -to A[4]
set_location_assignment PIN_33 -to A[5]
set_location_assignment PIN_24 -to A[6]
set_location_assignment PIN_12 -to A[7]
set_location_assignment PIN_26 -to RD_n
set_location_assignment PIN_5 -to WR_n
set_location_assignment PIN_27 -to IORQ_n
set_location_assignment PIN_9 -to SPI_CS
set_location_assignment PIN_4 -to SPI_MISO
set_location_assignment PIN_6 -to SPI_MOSI
set_location_assignment PIN_8 -to SPI_SCLK
set_location_assignment PIN_40 -to SPI_RDY
set_location_assignment PIN_31 -to BUSDIR_n
set_location_assignment PIN_28 -to WAIT_n
